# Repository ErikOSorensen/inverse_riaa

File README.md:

#  Inverse RIAA filter

Inverse RIAA filter for testing phono preamps. If we want to test phono preamps with
a soundcard interface, we need a lot of attenuation of the soundcard output - and we
would also like to invert the RIAA filtering that is part of an ordinary phono 
preamp such that the soundcard input receives a signal which, under ideal operation,
has a constant amplitude as the frequency varies.

## The schematic

The design is a simple and direct implementation of the suggestion of Lipshitz and Jung (1980),
in their paper "A High Accuracy Inverse RIAA Network" (Figure 3). I have adapted it by paralleling
some parts for greater accuracy.

## First physical build

This is a passive filter. I have built one into a Hammond 1455N1201BK extruded box,
with isolated (stereo) BNCs in and out. There is an option to add 20 dB of attenuation
for testing MC phono preamps.

For this first build I have used Susumu 0.5% resistors and Murata 1% capacitors.

## Characterization

Measurement of the attenuation and comparison to what we should expect (calculated
in LT spice) indicates that the filter is within 0.2 dB of the correct curve over
most of the frequency range.

Note that the measurements (in the MM path) were taken with an Analog Discovery
2, which only has a 14 bit ADC, so there is a lot of noise and quantization
error at the lower frequencies where attenuation is greatest. With the AD2, the
dynamic range is not sufficient to test the MC path, but since that only
involves a single extra resistor (which can be verified with a DMM), that
shouldn't involve any additional concerns.

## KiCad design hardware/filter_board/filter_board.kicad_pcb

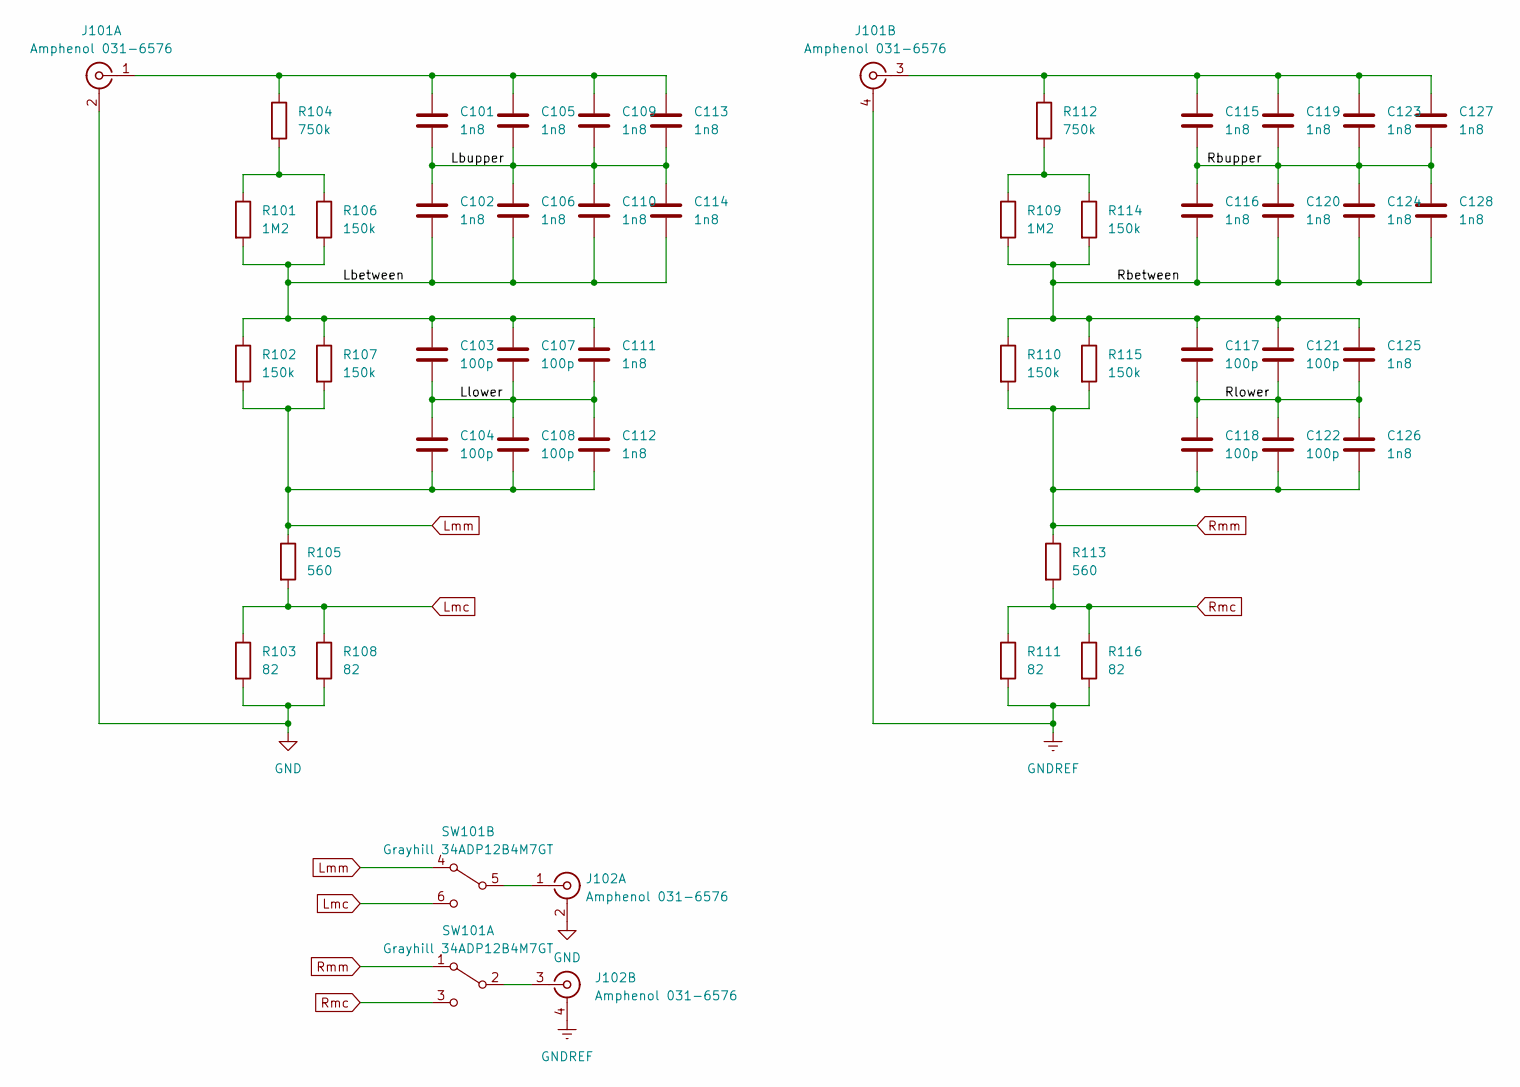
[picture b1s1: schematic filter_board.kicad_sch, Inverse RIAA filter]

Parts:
C101, C102, C105, C106, C109, C110, C111, C112, C113, C114, C115, C116, C119, C120, C123, C124, C125, C126, C127, C128: 1n8; C_0805_2012Metric
C103, C104, C107, C108, C117, C118, C121, C122: 100p; C_0805_2012Metric
J101, J102: Amphenol 031-6576; BNC_Amphenol_031-6575_Horizontal
R101, R109: 1M2; R_0805_2012Metric
R102, R106, R107, R110, R114, R115: 150k; R_0805_2012Metric
R103, R108, R111, R116: 82; R_0805_2012Metric
R104, R112: 750k; R_0805_2012Metric
R105, R113: 560; R_0805_2012Metric
SW101: Grayhill 34ADP12B4M7GT; 34ADP12B4M7GT

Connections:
/Lbetween: C102.2, C103.1, C106.2, C107.1, C110.2, C111.1, C114.2, R101.2, R102.1, R106.2, R107.1
/Lbupper: C101.2, C102.1, C105.2, C106.1, C109.2, C110.1, C113.2, C114.1
/Llower: C103.2, C104.1, C107.2, C108.1, C111.2, C112.1
/Rbetween: C116.2, C117.1, C120.2, C121.1, C124.2, C125.1, C128.2, R109.2, R110.1, R114.2, R115.1
/Rbupper: C115.2, C116.1, C119.2, C120.1, C123.2, C124.1, C127.2, C128.1
/Rlower: C117.2, C118.1, C121.2, C122.1, C125.2, C126.1
GND: J101.2 (Ext1), J102.2 (Ext1), R103.2, R108.2
GNDREF: J101.4 (Ext2), J102.4 (Ext2), R111.2, R116.2
Lmc: R103.1, R105.2, R108.1, SW101.6 (C)
Lmm: C104.2, C108.2, C112.2, R102.2, R105.1, R107.2, SW101.4 (A)
unnamed: C101.1, C105.1, C109.1, C113.1, J101.1 (In1), R104.1
unnamed: C115.1, C119.1, C123.1, C127.1, J101.3 (In2), R112.1
unnamed: J102.1 (In1), SW101.5 (B)
unnamed: J102.3 (In2), SW101.2 (B)
unnamed: R101.1, R104.2, R106.1
unnamed: R109.1, R112.2, R114.1
Rmc: R111.1, R113.2, R116.1, SW101.3 (C)
Rmm: C118.2, C122.2, C126.2, R110.2, R113.1, R115.2, SW101.1 (A)

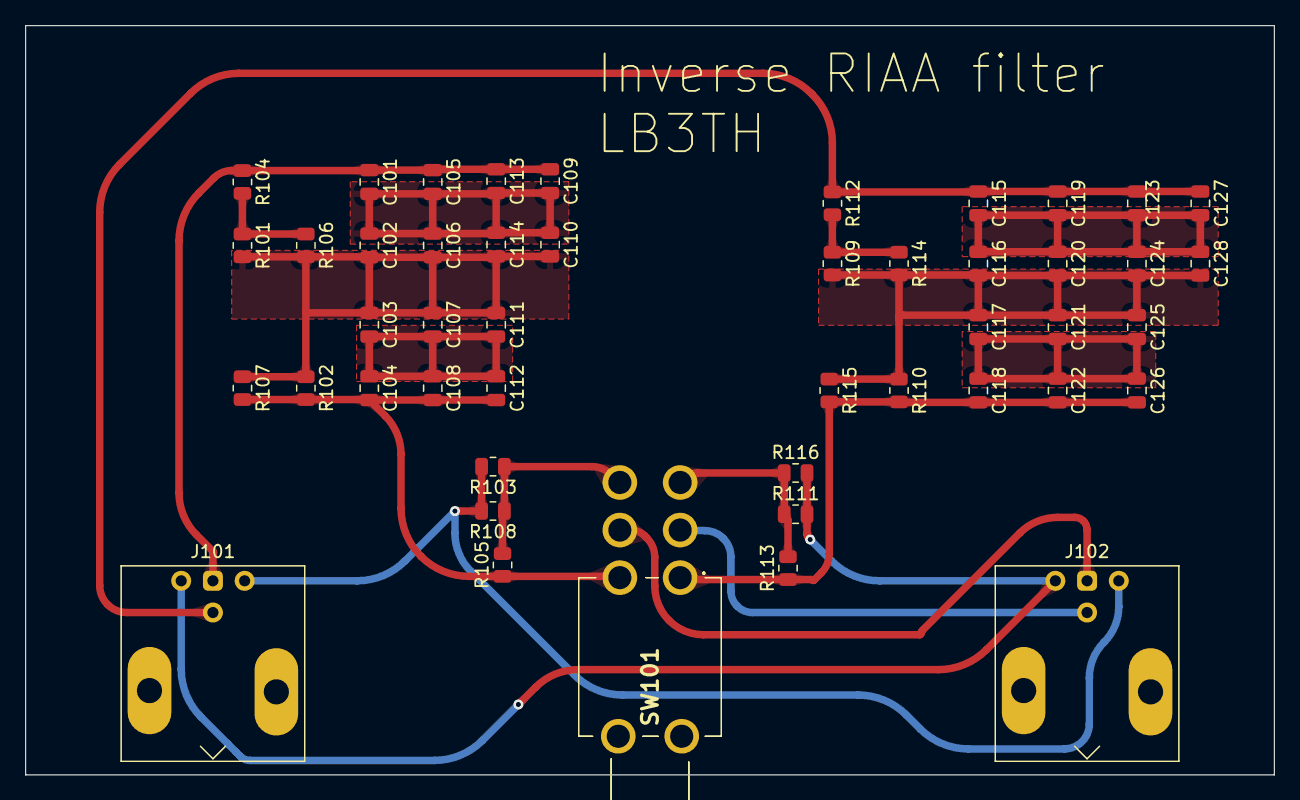
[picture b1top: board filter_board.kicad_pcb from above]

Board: 2 copper layers, 100.0 x 60.0 mm, 47 parts (0 on the bottom side), 18 nets.

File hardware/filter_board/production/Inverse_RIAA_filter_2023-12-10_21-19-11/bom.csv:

Designator,Footprint,Quantity,Value,LCSC Part #
"C101, C102, C105, C106, C109, C110, C111, C112, C113, C114, C115, C116, C119, C120, C123, C124, C125, C126, C127, C128",0805,20,1n8,
"C103, C104, C107, C108, C117, C118, C121, C122",0805,8,100p,
"J101, J102",BNC_Amphenol_031-6575_Horizontal,2,Amphenol 031-6576,
"R101, R109",0805,2,1M2,
"R102, R106, R107, R110, R114, R115",0805,6,150k,
"R103, R108, R111, R116",0805,4,82,
"R104, R112",0805,2,750k,
"R105, R113",0805,2,560,
SW101,34ADP12B4M7GT,1,Grayhill 34ADP12B4M7GT,

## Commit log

2023-12-10 Simulations.
2023-12-10 Filter board layout.
2023-12-10 Front panel for Hammond extruded case.
2023-12-22 Expected results (exported from LT spice).
2023-12-22 Frequency response measurements (Analog Discovery 2).
2023-12-22 Syncronizing with hardware files.
2023-12-22 Production files and updated README
2023-12-22 Added github reference in schematic.
2023-12-23 Measurements into graphs.
2023-12-23 added clarification
2023-12-23 More about design.
2023-12-23 minor
2023-12-23 typo
2023-12-23 Comment on MC.
2023-12-23 Issues moved from README to github issues.
